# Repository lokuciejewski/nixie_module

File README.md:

# Small module for standalone I2C control over Nixie Tube

This module is a small, low cost controller board for a nixie `z5740m` tube (and some compatible tubes, like `z5730`). It is based on the `ch32v003` microcontroller and is using a i2c protocol for communication with external host.
The board needs both VCC (either 3.3V or 5V) and the voltage for the tube (usually around 170V DC).

The module works in tandem with the [controller board](https://github.com/lokuciejewski/nixie_controller):

## Building

Prerequisites are:

- GCC or other C compiler
- [ch32fun](https://github.com/cnlohr/ch32fun) stack
- GNU make

Clone the `ch32fun` into the root folder of this project. Then run `make build` to compile the firmware.

## Programming

A ch32v003 programmer is required (for example the WCH-Link-E). Connect the programmer to the VCC, GND and SWIO pins and run `make flash`.

## Communication over i2c bus

By default, this module starts with the address `0x40` (0x20 << 1, see [main.c](./main.c)).
After that, a new address can be written over the i2c which will be saved into the flash and the module will subsequently answer on the new address.

Communication over the i2c bus is a standard way, except there is no auto increment of the register when reading.

### I2c registers

This device contains the following i2c registers:

- I2cReg_Address -> `0x00` - used to set a new i2c address for the device
- I2cReg_NixieValue -> `0x01` - read or write the current digit that should be displayed
- I2cReg_HvValueLowByte -> `0x02` - read the high byte of the current High Voltage reading
- I2cReg_HvValueHighByte -> `0x03` - read the low byte of the current High Voltage reading
- I2cReg_NixiePwmValue -> `0x04` - read or write the new PWM brightness value (0-100)
- I2cReg_NixieBrightnessCompensation -> `0x05` - turn on or off brightness compensation (this reduces the brightness of the main digit if the commma is on)

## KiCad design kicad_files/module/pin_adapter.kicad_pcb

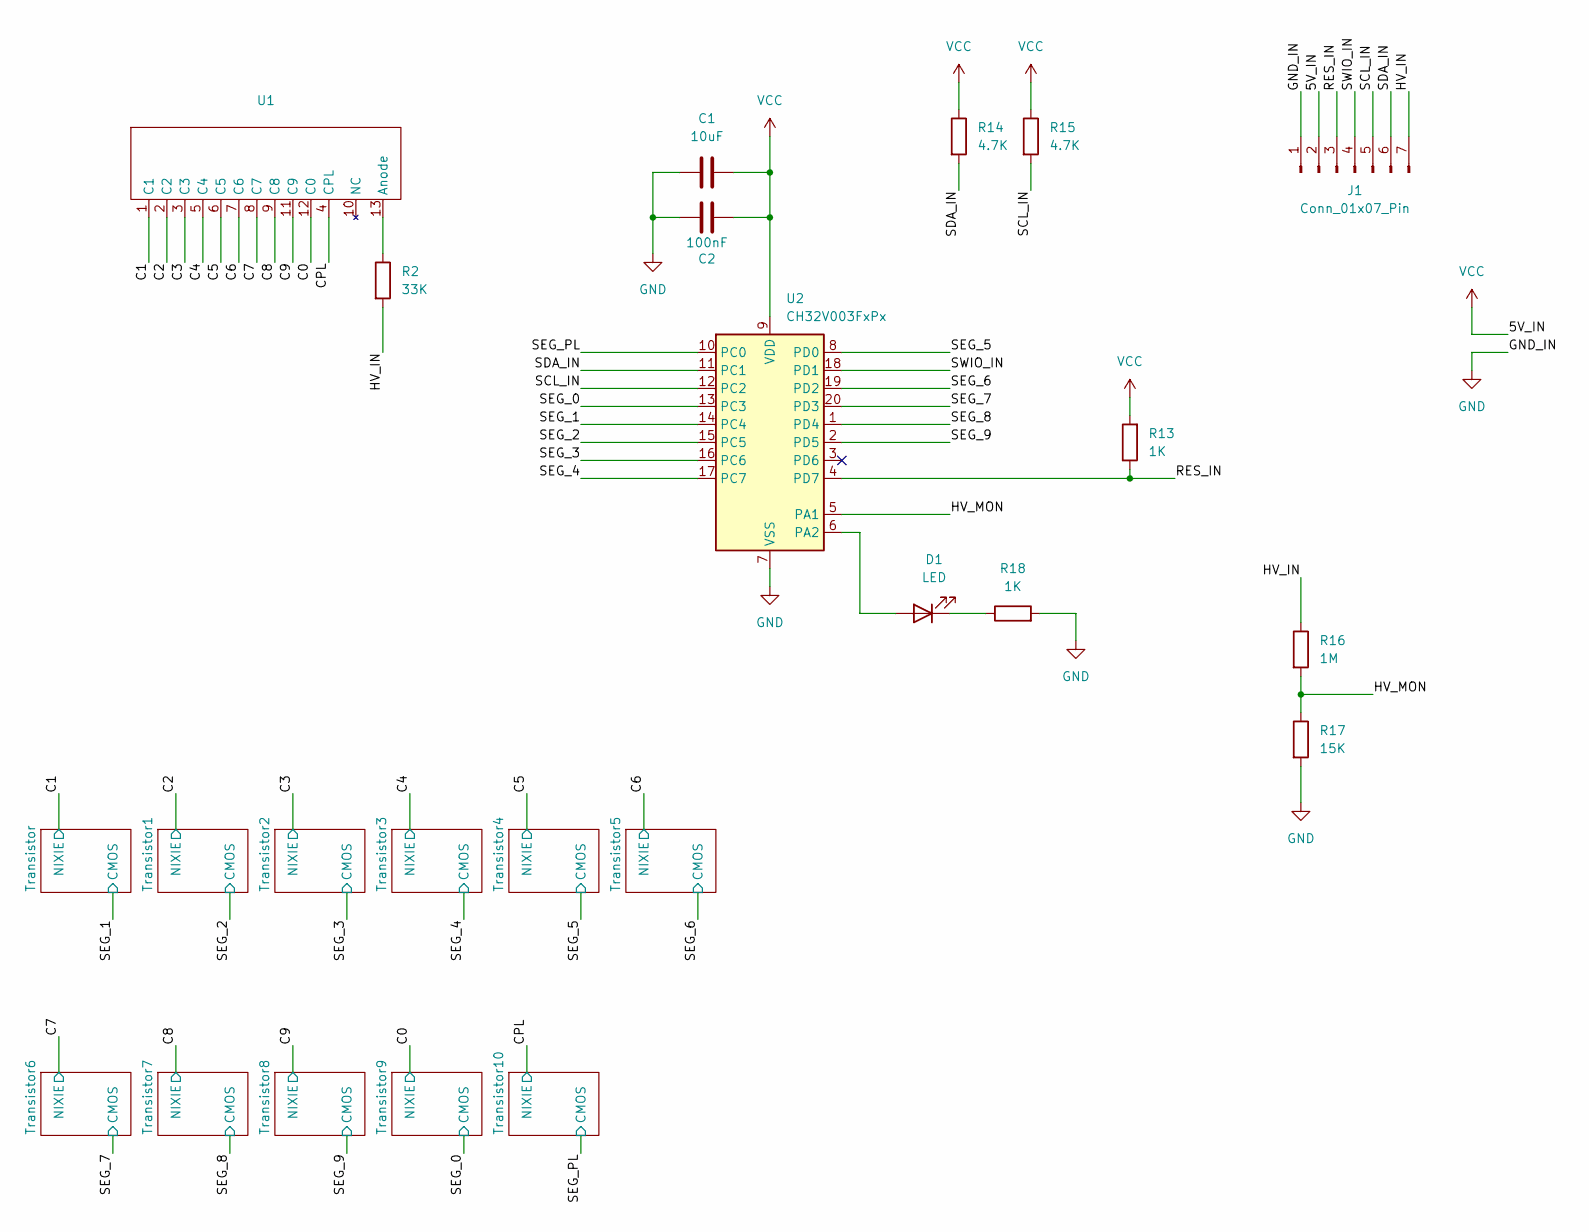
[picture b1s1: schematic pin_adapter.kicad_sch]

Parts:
C1: 10uF; C_0603_1608Metric_Pad1.08x0.95mm_HandSolder
C2: 100nF; C_0603_1608Metric_Pad1.08x0.95mm_HandSolder
D1: LED; LED_0603_1608Metric_Pad1.05x0.95mm_HandSolder
J1: Conn_01x07_Pin; PinHeader_1x07_P2.54mm_Vertical
R2: 33K; R_1206_3216Metric_Pad1.30x1.75mm_HandSolder
R13, R18: 1K; R_0603_1608Metric_Pad0.98x0.95mm_HandSolder
R14, R15: 4.7K; R_0603_1608Metric_Pad0.98x0.95mm_HandSolder
R16: 1M; R_0603_1608Metric_Pad0.98x0.95mm_HandSolder
R17: 15K; R_0603_1608Metric_Pad0.98x0.95mm_HandSolder
U1: z5740m
U2: CH32V003FxPx; TSSOP-20_4.4x6.5mm_P0.65mm

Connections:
/C0: U1.12 (C0); also elsewhere on the board
/C1: U1.1 (C1); also elsewhere on the board
/C2: U1.2 (C2); also elsewhere on the board
/C3: U1.3 (C3); also elsewhere on the board
/C4: U1.5 (C4); also elsewhere on the board
/C5: U1.6 (C5); also elsewhere on the board
/C6: U1.7 (C6); also elsewhere on the board
/C7: U1.8 (C7); also elsewhere on the board
/C8: U1.9 (C8); also elsewhere on the board
/C9: U1.11 (C9); also elsewhere on the board
/CPL: U1.4 (CPL); also elsewhere on the board
/HV_IN: J1.7, R2.2, R16.1
/HV_MON: R16.2, R17.1, U2.5 (PA1)
/RES_IN: J1.3, R13.1, U2.4 (PD7)
/SCL_IN: J1.5, R15.2, U2.12 (PC2)
/SDA_IN: J1.6, R14.2, U2.11 (PC1)
/SEG_0: U2.13 (PC3); also elsewhere on the board
/SEG_1: U2.14 (PC4); also elsewhere on the board
/SEG_2: U2.15 (PC5); also elsewhere on the board
/SEG_3: U2.16 (PC6); also elsewhere on the board
/SEG_4: U2.17 (PC7); also elsewhere on the board
/SEG_5: U2.8 (PD0); also elsewhere on the board
/SEG_6: U2.19 (PD2); also elsewhere on the board
/SEG_7: U2.20 (PD3); also elsewhere on the board
/SEG_8: U2.1 (PD4); also elsewhere on the board
/SEG_9: U2.2 (PD5); also elsewhere on the board
/SEG_PL: U2.10 (PC0); also elsewhere on the board
/SWIO_IN: J1.4, U2.18 (PD1)
GND: C1.1, C2.2, J1.1, R17.2, R18.2, U2.7 (VSS); also elsewhere on the board
unnamed: D1.2 (A), U2.6 (PA2)
unnamed: D1.1 (K), R18.1
unnamed: R2.1, U1.13 (Anode)
VCC: C1.2, C2.1, J1.2, R13.2, R14.1, R15.1, U2.9 (VDD)

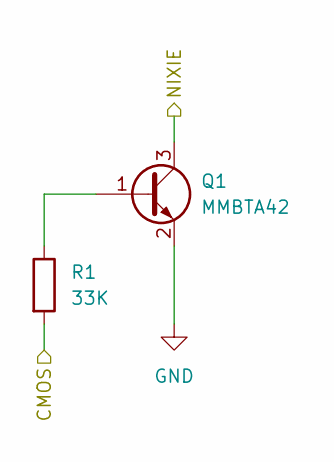
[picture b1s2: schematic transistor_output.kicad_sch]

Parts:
Q1: MMBTA42; SOT-23
R1: 33K; R_0603_1608Metric_Pad0.98x0.95mm_HandSolder

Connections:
/C1: Q1.3 (C); also elsewhere on the board
/SEG_1: R1.2; also elsewhere on the board
GND: Q1.2 (E); also elsewhere on the board
unnamed: Q1.1 (B), R1.1

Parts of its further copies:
Q2, Q3, Q4, Q5, Q6, Q7, Q8, Q9, Q10, Q11: MMBTA42; SOT-23
R3, R4, R5, R6, R7, R8, R9, R10, R11, R12: 33K; R_0603_1608Metric_Pad0.98x0.95mm_HandSolder

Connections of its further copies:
/C0: Q10.3 (C); also elsewhere on the board
/C2: Q2.3 (C); also elsewhere on the board
/C3: Q3.3 (C); also elsewhere on the board
/C4: Q4.3 (C); also elsewhere on the board
/C5: Q5.3 (C); also elsewhere on the board
/C6: Q6.3 (C); also elsewhere on the board
/C7: Q7.3 (C); also elsewhere on the board
/C8: Q8.3 (C); also elsewhere on the board
/C9: Q9.3 (C); also elsewhere on the board
/CPL: Q11.3 (C); also elsewhere on the board
/SEG_0: R11.2; also elsewhere on the board
/SEG_2: R3.2; also elsewhere on the board
/SEG_3: R4.2; also elsewhere on the board
/SEG_4: R5.2; also elsewhere on the board
/SEG_5: R6.2; also elsewhere on the board
/SEG_6: R7.2; also elsewhere on the board
/SEG_7: R8.2; also elsewhere on the board
/SEG_8: R9.2; also elsewhere on the board
/SEG_9: R10.2; also elsewhere on the board
/SEG_PL: R12.2; also elsewhere on the board
GND: Q2.2 (E), Q3.2 (E), Q4.2 (E), Q5.2 (E), Q6.2 (E), Q7.2 (E), Q8.2 (E), Q9.2 (E), Q10.2 (E), Q11.2 (E); also elsewhere on the board
unnamed: Q2.1 (B), R3.1
unnamed: Q3.1 (B), R4.1
unnamed: Q4.1 (B), R5.1
unnamed: Q5.1 (B), R6.1
unnamed: Q6.1 (B), R7.1
unnamed: Q7.1 (B), R8.1
unnamed: Q8.1 (B), R9.1
unnamed: Q9.1 (B), R10.1
unnamed: Q10.1 (B), R11.1
unnamed: Q11.1 (B), R12.1

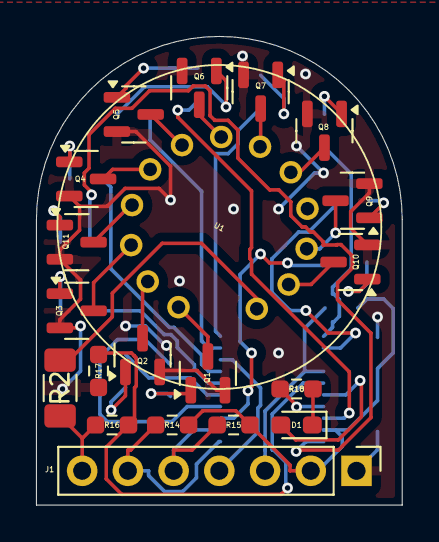
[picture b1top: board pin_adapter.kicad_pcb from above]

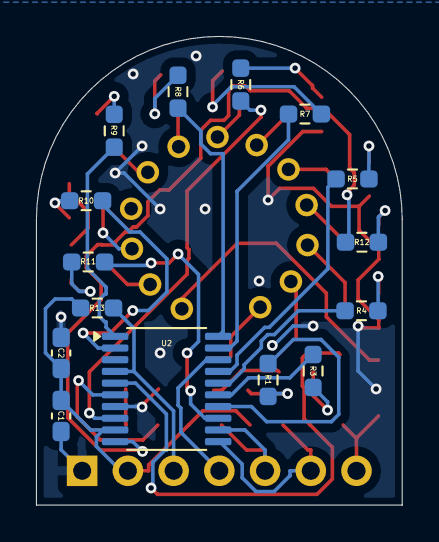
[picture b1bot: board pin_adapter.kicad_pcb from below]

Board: 2 copper layers, 20.3 x 26.0 mm, 35 parts (15 on the bottom side), 44 nets.

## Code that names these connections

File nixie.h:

#pragma once
#include "ch32fun/ch32fun/ch32fun.h"
#include "stdbool.h"
#include "stdint.h"

typedef enum {
    NIXIE_SEG_0 = PC3,
    NIXIE_SEG_1 = PC4,
    NIXIE_SEG_2 = PC5,
    NIXIE_SEG_3 = PC6,
    NIXIE_SEG_4 = PC7,
    NIXIE_SEG_5 = PD0,
    NIXIE_SEG_6 = PD2,
    NIXIE_SEG_7 = PD3,
    NIXIE_SEG_8 = PD4,
    NIXIE_SEG_9 = PD5,
    NIXIE_SEG_PL = PC0,
    NIXIE_SEG_NO_SEG = 0xff,
} NixieSegment;

void Nixie_Init(void);
/// Should be called periodically for software PWM
void Nixie_PWM_RefreshEvery500us(void);
/// Value needs to be between 0 and 20 for 0% to 100%
void Nixie_PWM_SetDutyCycle(uint8_t new_duty_cycle);
void Nixie_DisplayRefresh(uint16_t delay_ms);
void Nixie_EnableCommaBrightnessCompensation(void);
void Nixie_DisableCommaBrightnessCompensation(void);

NixieSegment Nixie_GetCurrentSeg(void);
bool Nixie_IsCommaOn(void);
uint8_t Nixie_ToUINT8(NixieSegment seg);
NixieSegment Nixie_FromUINT8(uint8_t seg);

void Nixie_TurnOn(NixieSegment seg);
void Nixie_TurnOff(void);
void Nixie_CommaOn(void);
void Nixie_CommaOff(void);

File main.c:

#include "ch32fun/ch32fun/ch32fun.h"
#include "i2c_slave.h"
#include "nixie.h"

#define LED_PIN PA2

typedef enum : uint8_t {
    I2cReg_Address = 0,
    I2cReg_NixieValue,
    I2cReg_HvValueLowByte,
    I2cReg_HvValueHighByte,
    I2cReg_NixiePwmValue,
    I2cReg_NixieBrightnessCompensation,
    I2cReg_Size,
} I2cRegisters_e;

#define I2C_DEFAULT_ADDRESS (uint8_t)(0x20)

#define SYSTEM_VOLTAGE_MV 3300U
#define HV_UPPER_LIMIT_MV 3300U
#define HV_LOWER_LIMIT_MV 2700U
#define HV_UPPER_LIMIT ((1000 * HV_UPPER_LIMIT_MV) / SYSTEM_VOLTAGE_MV)
#define HV_LOWER_LIMIT ((1000 * HV_LOWER_LIMIT_MV) / SYSTEM_VOLTAGE_MV)

#define DEFAULT_LOOP_TIME_US 450U

volatile uint8_t i2c_registers[I2cReg_Size - 1] = {0x00};
bool change_address = false;
uint8_t new_i2c_address = 0x00;
uint8_t* i2c_address = (uint8_t*)0x08003700;

bool unsafe_hv = true;

void onWrite(uint8_t reg, uint8_t length) {
    switch ((I2cRegisters_e)reg) {
    case I2cReg_Address:
        if (*i2c_address != i2c_registers[I2cReg_Address]) {
            change_address = true;
            new_i2c_address = i2c_registers[I2cReg_Address];
        }
        break;

    case I2cReg_NixieValue:
        if (!unsafe_hv) {
            if (i2c_registers[reg] != 0xff) {
                Nixie_TurnOn(Nixie_FromUINT8(i2c_registers[reg] & 0b1111));
                if ((i2c_registers[I2cReg_NixieValue] & 0b10000000) != 0) {
                    Nixie_CommaOn();
                } else {
                    Nixie_CommaOff();
                }
                break;
            } else {
                Nixie_TurnOff();
            }
            i2c_registers[I2cReg_NixieValue] = Nixie_GetCurrentSeg();
        }
        break;
    case I2cReg_NixiePwmValue:
        Nixie_PWM_SetDutyCycle(i2c_registers[I2cReg_NixiePwmValue]);
        break;
    case I2cReg_NixieBrightnessCompensation:
        // TODO: implement
        break;

    default:
        break;
    }
}

void onRead(uint8_t reg) {}

static void unlockFlash(void) {
    FLASH->KEYR = FLASH_KEY1;
    FLASH->KEYR = FLASH_KEY2;
    while (FLASH->STATR & FLASH_STATR_BSY) {
    }
}

static void unlockProgramming(void) {
    FLASH->MODEKEYR = FLASH_KEY1;
    FLASH->MODEKEYR = FLASH_KEY2;
    while (FLASH->STATR & FLASH_STATR_BSY) {
    }
}

static void changeAddress(void) {
    unlockFlash();
    unlockProgramming();
    // Erase page
    FLASH->CTLR = CR_PAGE_ER;
    FLASH->ADDR = (intptr_t)i2c_address;
    FLASH->CTLR = CR_STRT_Set | CR_PAGE_ER;
    // Page erase takes about 3ms
    while (FLASH->STATR & FLASH_STATR_BSY) {
    }

    if (*i2c_address != 0xff) {
        while (1) // Flash erase didn't work
        {
        }
    }
    // Clear buffer and prepare for flashing
    FLASH->CTLR = CR_PAGE_PG;
    FLASH->CTLR = CR_BUF_RST | CR_PAGE_PG;
    FLASH->ADDR = (intptr_t)i2c_address;
    while (FLASH->STATR & FLASH_STATR_BSY) // Not really needed
    {
    }
    // Write to the memory
    for (uint8_t i = 0; i < 16; i++) {
        ((uint32_t*)i2c_address)[i] = (uint32_t)new_i2c_address;
        FLASH->CTLR = CR_PAGE_PG | FLASH_CTLR_BUF_LOAD; // Load the buffer.
        while (FLASH->STATR &
               FLASH_STATR_BSY) // Only needed if running from RAM.
        {
        }
    }

    // Actually write the flash out. (Takes about 3ms)
    FLASH->CTLR = CR_PAGE_PG | CR_STRT_Set;

    while (FLASH->STATR & FLASH_STATR_BSY) {
    }

    if (*i2c_address != new_i2c_address) {
        while (1) // Flash write didn't work
        {
        }
    }
    // Perform software reset
    PFIC->SCTLR |= 0x80000000;
}

int main() {
    SystemInit();
    funGpioInitAll();
    funAnalogInit();

    // Initialise led
    funPinMode(LED_PIN, GPIO_Speed_10MHz | GPIO_CNF_OUT_PP);
    // Initialise adc - high voltage monitoring
    funPinMode(PA1, GPIO_CFGLR_IN_ANALOG);

    funDigitalWrite(LED_PIN, FUN_HIGH);
    Nixie_Init();

    // Initialize I2C slave
    funPinMode(PC1, GPIO_CFGLR_OUT_10Mhz_AF_OD); // SDA
    funPinMode(PC2, GPIO_CFGLR_OUT_10Mhz_AF_OD); // SCL

    if (*i2c_address == 0xff) {
        // Address not set yet, use I2C_DEFAULT_ADDRESS
        SetupI2CSlave(I2C_DEFAULT_ADDRESS, i2c_registers, sizeof(i2c_registers),
                      onWrite, onRead, false);
        i2c_registers[I2cReg_Address] = I2C_DEFAULT_ADDRESS;
    } else {
        SetupI2CSlave(*i2c_address, i2c_registers, sizeof(i2c_registers),
                      onWrite, onRead, false);
        i2c_registers[I2cReg_Address] = *i2c_address;
    }

    i2c_registers[I2cReg_NixieValue] = 0xff; // Nixie off

    Delay_Ms(10); // Just to make sure the led blinks
    funDigitalWrite(LED_PIN, FUN_LOW);

    uint16_t hv_value = 0;

    while (1) {
        if (change_address) {
            funDigitalWrite(LED_PIN, FUN_HIGH);
            changeAddress();
        }
        hv_value = (uint16_t)funAnalogRead(ANALOG_1);
        i2c_registers[I2cReg_HvValueLowByte] = (uint8_t)(hv_value & 0xff);
        i2c_registers[I2cReg_HvValueHighByte] = (uint8_t)(hv_value >> 8);
        // unsafe_hv = hv_value > HV_UPPER_LIMIT;
        unsafe_hv =
            false; // TODO: replace 20k resistor with 15k to measure voltage
        if (unsafe_hv) {
            Nixie_CommaOff();
            Nixie_TurnOff();
            funDigitalWrite(LED_PIN, FUN_HIGH);
        } else {
            funDigitalWrite(LED_PIN, FUN_LOW);
            Nixie_PWM_RefreshEvery500us();
        }
        Delay_Us(DEFAULT_LOOP_TIME_US);
    }
}

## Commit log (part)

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2025-04-06 added readme
2025-04-06 added gitignore
2025-08-25 sample 1 changes
2025-08-25 fixed comma on
2025-12-30 formatting changes
2025-12-30 added clang-format, added soft PWM (WIP), minor fixes
2025-12-30 added missing files, added PWM control + PWM compensation on comma on
2025-12-30 increased PWM resolution to 0.5ms
2026-01-06 fixed NIXIE_SEG_NO_SEG being equal to NIXIE_SEG_0, removed refresh trigger from i2c
2026-01-06 fixed i2c regs size, changed pwm_value to 32-bit
2026-01-09 added turning off all numeric segments to prevent glitches
